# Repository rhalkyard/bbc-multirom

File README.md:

# MultiROM: A low-cost BBC Master / Electron ROM cartridge

There are plenty of perfectly-good options for building ROM cartridges for the BBC Master and Acorn Electron Plus One. However, I am a stubborn git and enjoy reinventing the wheel for fun, so I decided to come up with my own take on the concept.

Rather than use the 27x and 28x series (E)EPROMS that were used Back In The Day, MultiROM uses a NOR Flash IC, the SST39SF010A. This part is much cheaper and more readily available than EEPROMs, but can still be obtained as a through-hole part for easy DIY assembly. Additionally, it offers more capacity (a whopping one megabit!), which MultiROM uses to store multiple ROM images on one cartridge, selected by DIP switches.

The schematic and PCB layout were produced using [KiCad 7.0](https://www.kicad.org/).

## How to build MultiROM

### Bill of Materials

Reference   | Part
------------|-------------------------------------------------------------
`C1`, `C2`  | Ceramic capacitor, 0.1μF
`RN1`       | SIP6 resistor network, bussed, 10KΩ
`SW1`       | SPST DIP switch module, 4 switches
`U1`        | SST39SF010 1Mbit flash memory, DIP32 package
`U2`        | GAL16V8 or ATF16V8 programmable logic device, DIP20 package

`RN1` can be omitted if you trust the weak pull-ups built into `U2`. I forgot to order it when building my prototypes, and they seem to work just fine without it.

`SW1` can be omitted if you want the cartridge to function as a basic 2x16k catridge without bank switching.

### PCB

Any PCB fabricator service such as PCBWay, OSHPark or JLCPCB should be able to fabricate the board. Some shops will accept the `.kicad_pcb` file directly, but most will require Gerber and drill files. These can be exported from Kicad using the File -> Fabrication Outputs menu options.

Ideally, the edge connector should have a chamfered board edge and hard gold-plated contacts, to avoid damaging the PCB socket and to ensure a good connection. These are usually extra-cost options that have to be requested when placing the order.

When assembling components onto the PCB, pay attention to which side they are on! Integrated Circuits `U1` and `U2` go on the *back* side of the PCB, with their orientation notches facing towards the edge connector.

This project uses [KiBot](https://github.com/INTI-CMNB/KiBot) to automate output in various formats from KiCad; release archives contain manufacturing files for various popular PCB fabricators.

### GAL

`U2` is a programmable GAL that provides selection and addressing logic compatible with both the Electron and BBC Master.

GALasm source for `U2` can be found in the `pld/` directory, see [the README in that folder](pld/README.md) for instructions on building and programming.

### Cartridge case

The MultiROM PCB is designed to fit in the 'standard' Master/Electron cartridge case produced by Acorn. I do not have a real cartridge to check this against, but I 3D-printed [Paul Boddie's OpenSCAD cartridge](https://hgweb.boddie.org.uk/AcornElectron) and it fits nicely in there.

If the bank-selection DIP switches (`SW1`) are installed, a suitable cutout will need to be made in the case.

Note that there is very little clearance for components inside the case - if the board is to fit inside the case, then the ICs must be soldered directly onto the board rather than socketed.

## How to use MultiROM

### Inserting the cartridge

With the machine powered off, insert MultiROM into either the front or rear cartridge slot. In the rear slot, MultiROM will appear as Sideways ROMs 0 and 1. In the front slot, it will appear as Sideways ROMs 2 and 3.

Keep in mind that the cartridge housing is the only thing preventing a cartridge from being inserted backwards! If using a bare MultiROM board, pay attention to the "This side to front" markings - the correct orientation is with the chips facing *away* from you.

### Switching banks

Each cartridge slot corresponds to two Sideways ROMs - 0 and 1 for the rear cartridge slot, and 2 and 3 for the front. The DIP switch `SW1` on the front of the cartridge allows one of four banks to be selected for each ROM, allowing multiple ROM images to be stored on the cartridge.

The left two switches select the bank for ROM 0 or 2, the right two switches select the bank for ROM 1 or 3.

While switching banks on a running machine is unlikely to cause any permanent harm, it will almost certainly cause the machine to crash the next time a ROM service call is issued. Always reset the machine after switching banks!

### Programming

#### In-System Programming

The [`tools/`](tools/) directory contains software suitable for either a Master or Electron, that can program MultiROM, query Sideways ROM slots, and save Sideways ROMs to tape or disc.

Source is in [BeebASM](https://github.com/stardot/beebasm) format.

#### Using an external programmer

The flash IC can be programmed in an external programmer according to the following memory map.

Address Range   | ROM       |Bank
----------------|-----------|----
00000-03FFF     | Low       | 0
04000-07FFF     | High      | 0
08000-0BFFF     | Low       | 1
0C000-0FFFF     | High      | 1
10000-13FFF     | Low       | 2
14000-17FFF     | High      | 2
18000-1BFFF     | Low       | 3
1C000-1FFFF     | High      | 3

## Technical details

The SST39SF010A is flash memory, and cannot be programmed like a regular EEPROM. Data can only be erased in 4kb sectors, and writes and erase operations are performed using command strings written to 'magic' addresses. Writes can only be made to erased memory. After issuing an erase or write command, the chip must be allowed to complete the operation before continuing.

Completion can be determined by repeatedly reading back the written byte - until the operation is complete, bit 7 will be inverted, and bit 6 will toggle with each subsequent read.

Since the programming process is so convoluted, and regular writes are ignored, a write protection jumper is not provided.

### Flash Commands

Writing, erasing, chip-status and chip-ID functions are accessed by performing a 'magic' sequence of writes, as described in the datasheet, to addresses `5555` and `2AAA`

Because the cartridge slots are mapped into memory starting at address `&8000`, and the low/high ROM select line is used as the 14th address bit, when programming flash on the machine, use the following addresses:

Flash address   | ROM      | BBC Address
----------------|----------|------------
`5555`          | 1 / 3    | `9555`
`2AAA`          | 0 / 2    | `AAAA`

E.g., to write a byte to ROM 0 (i.e. the low ROM in the front cartridge socket), assuming that the sector has been erased:

1. Page in ROM 1
2. Write `&AA` to `&9555`
3. Page in ROM 0
4. Write `&55` to `&AAAA`
5. Page in ROM 1
6. Write `&A0` to `&9555`
7. Page in ROM 0
8. Write a byte to the desired address
9. Repeatedly read back any ROM address until two consecutive reads yield the same data.

This process must be repeated for each byte.

Any spurious reads or writes occurring during this process will cancel the operation or cause undesirable effects - to prevent MOS from interfering it is advisable to disable IRQ interrupts with an `SEI` instruction.

### Example Code

[`tools/flashio.6502`](tools/flashio.6502) contains utility routines for erasing and programming the flash, and safely querying its ID bytes without corrupting Sideways RAM. These were written for use by the tools in that directory, but are heavily commented and designed to be reused.

## TODO

- [ ] Modify [Paul Boddie's OpenSCAD cartridge case](https://hgweb.boddie.org.uk/AcornElectron) to have a cutout for the DIP switches (and maybe cutouts for IC sockets too?).

- [ ] Recruit a volunteer to test cartridge and software functionality on Electron.

## References

- [Phillip Pearson's Electron flash cartridge](https://github.com/google/myelin-acorn-electron-hardware/tree/main/32kb_flash_cartridge) - uses SST39SF010A, but can't be written on a Master, and does not have bank switching.

- [Stardot thread for Retro Hardware ARA III](https://stardot.org.uk/forums/viewtopic.php?t=15629) - writeable cartridge that uses a GAL to support both Electron and Master, but uses expensive 28C256 EEPROM.

- [BooBip.com Sideways Flash Module](http://www.boobip.com/hardware/128kb-flash) - another SST39SF010A-based ROM replacement, designed to plug into internal Sideways ROM sockets.

- [Acorn Application Note 014: Acorn Electron Cartridge Interface Specification](http://chrisacorns.computinghistory.org.uk/docs/Acorn/AN/014.pdf) - Official cartridge interface specs, including differences between Electron and Master.

- [BeebWiki article on Sideways ROM](https://beebwiki.mdfs.net/Paged_ROM) - especially the section on the Electron and its ROM-selection quirks. See also, this [Stardot post](https://stardot.org.uk/forums/viewtopic.php?p=6681#6681) with a technical background on the Electron's ROM selection register.

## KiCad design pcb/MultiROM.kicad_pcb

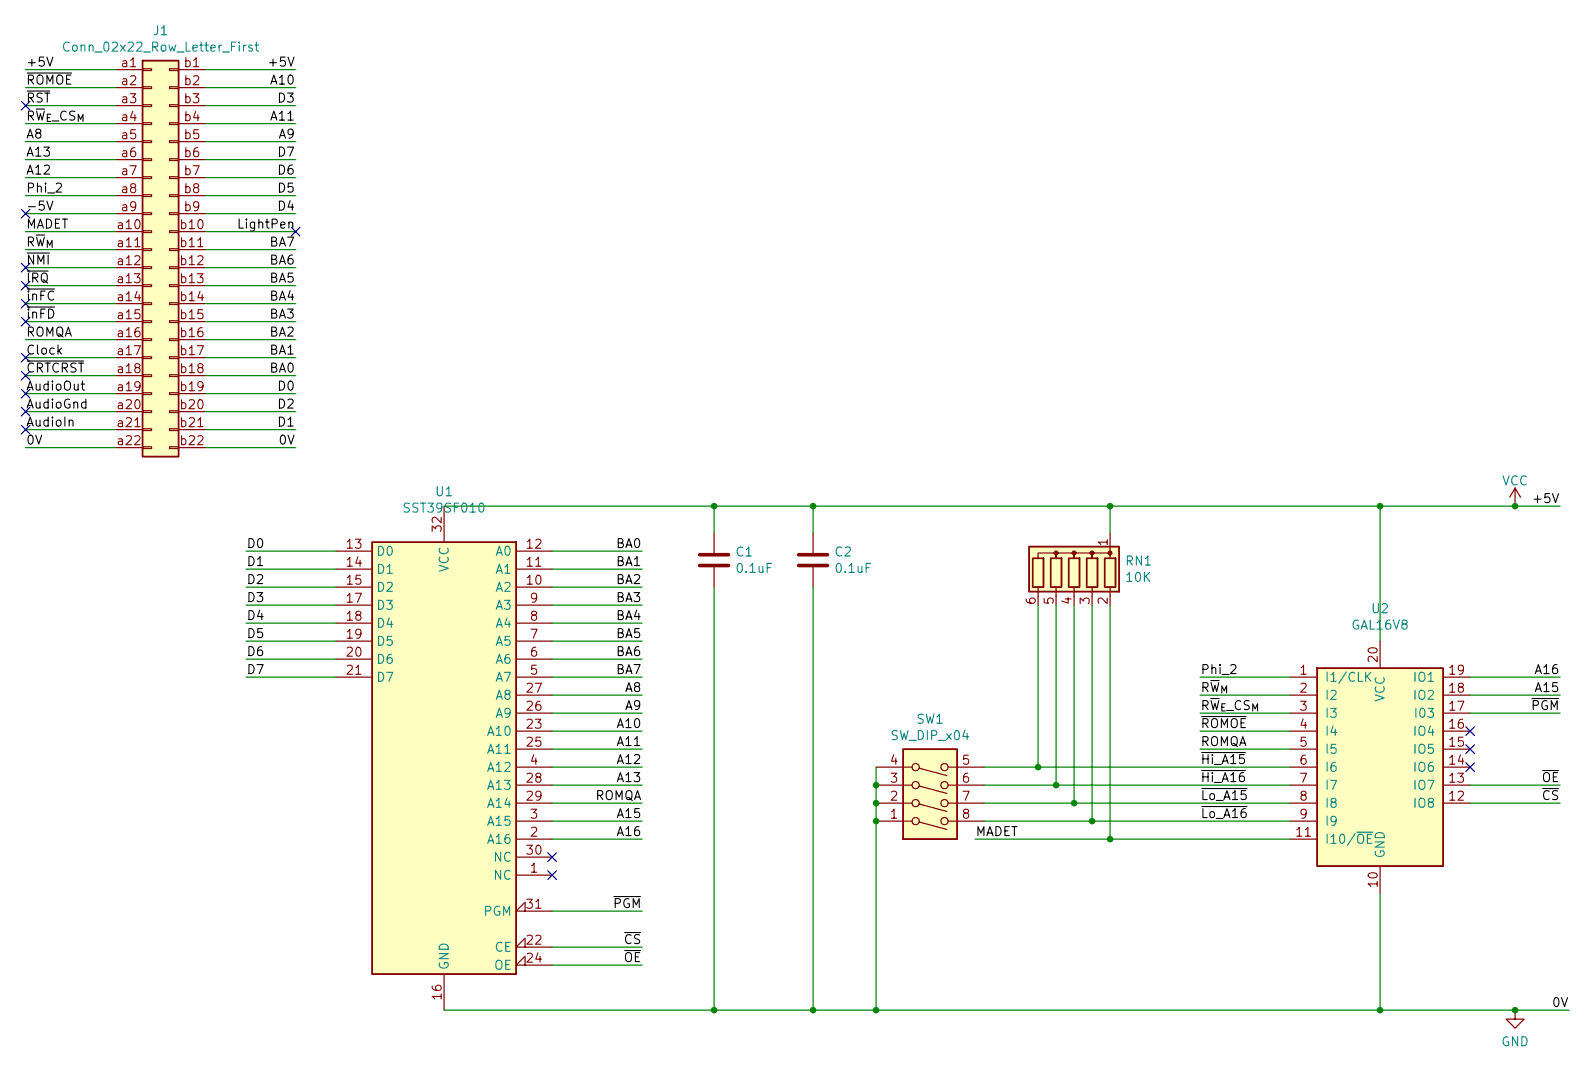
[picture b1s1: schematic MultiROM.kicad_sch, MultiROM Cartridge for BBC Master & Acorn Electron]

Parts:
C1, C2: 0.1uF; C_Disc_D3.0mm_W1.6mm_P2.50mm
J1: Conn_02x22_Row_Letter_First; bbc-master-acorn-electron-cartridge
RN1: 10K; R_Array_SIP6
SW1: SW_DIP_x04; SW_DIP_SPSTx04_Piano_10.8x11.72mm_W7.62mm_P2.54mm
U1: SST39SF010; DIP-32_W15.24mm
U2: GAL16V8; DIP-20_W7.62mm

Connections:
/-5V: J1.a9
/A8: J1.a5, U1.27 (A8)
/A9: J1.b5, U1.26 (A9)
/A10: J1.b2, U1.23 (A10)
/A11: J1.b4, U1.25 (A11)
/A12: J1.a7, U1.4 (A12)
/A13: J1.a6, U1.28 (A13)
/A15: U1.3 (A15), U2.18 (IO2)
/A16: U1.2 (A16), U2.19 (IO1)
/AudioGnd: J1.a20
/AudioIn: J1.a21
/AudioOut: J1.a19
/BA0: J1.b18, U1.12 (A0)
/BA1: J1.b17, U1.11 (A1)
/BA2: J1.b16, U1.10 (A2)
/BA3: J1.b15, U1.9 (A3)
/BA4: J1.b14, U1.8 (A4)
/BA5: J1.b13, U1.7 (A5)
/BA6: J1.b12, U1.6 (A6)
/BA7: J1.b11, U1.5 (A7)
/Clock: J1.a17
/D0: J1.b19, U1.13 (D0)
/D1: J1.b21, U1.14 (D1)
/D2: J1.b20, U1.15 (D2)
/D3: J1.b3, U1.17 (D3)
/D4: J1.b9, U1.18 (D4)
/D5: J1.b8, U1.19 (D5)
/D6: J1.b7, U1.20 (D6)
/D7: J1.b6, U1.21 (D7)
/LightPen: J1.b10
/MADET: J1.a10, RN1.2 (R1), U2.11 (I10/~OE)
/Phi_2: J1.a8, U2.1 (I1/CLK)
/ROMQA: J1.a16, U1.29 (A14), U2.5 (I5)
/R~W_{E}_CS_{M}: J1.a4, U2.3 (I3)
/R~W_{M}: J1.a11, U2.2 (I2)
/~CRTCRST: J1.a18
/~CS: U1.22 (CE), U2.12 (IO8)
/~Hi_A15: RN1.6 (R5), SW1.5, U2.6 (I6)
/~Hi_A16: RN1.5 (R4), SW1.6, U2.7 (I7)
/~IRQ: J1.a13
/~Lo_A15: RN1.4 (R3), SW1.7, U2.8 (I8)
/~Lo_A16: RN1.3 (R2), SW1.8, U2.9 (I9)
/~NMI: J1.a12
/~OE: U1.24 (OE), U2.13 (IO7)
/~PGM: U1.31 (PGM), U2.17 (I03)
/~ROMOE: J1.a2, U2.4 (I4)
/~RST: J1.a3
/~inFC: J1.a14
/~inFD: J1.a15
GND: C1.2, C2.2, J1.a22, J1.b22, SW1.1, SW1.2, SW1.3, SW1.4, U1.16 (GND), U2.10 (GND)
VCC: C1.1, C2.1, J1.a1, J1.b1, RN1.1 (common), U1.32 (VCC), U2.20 (VCC)

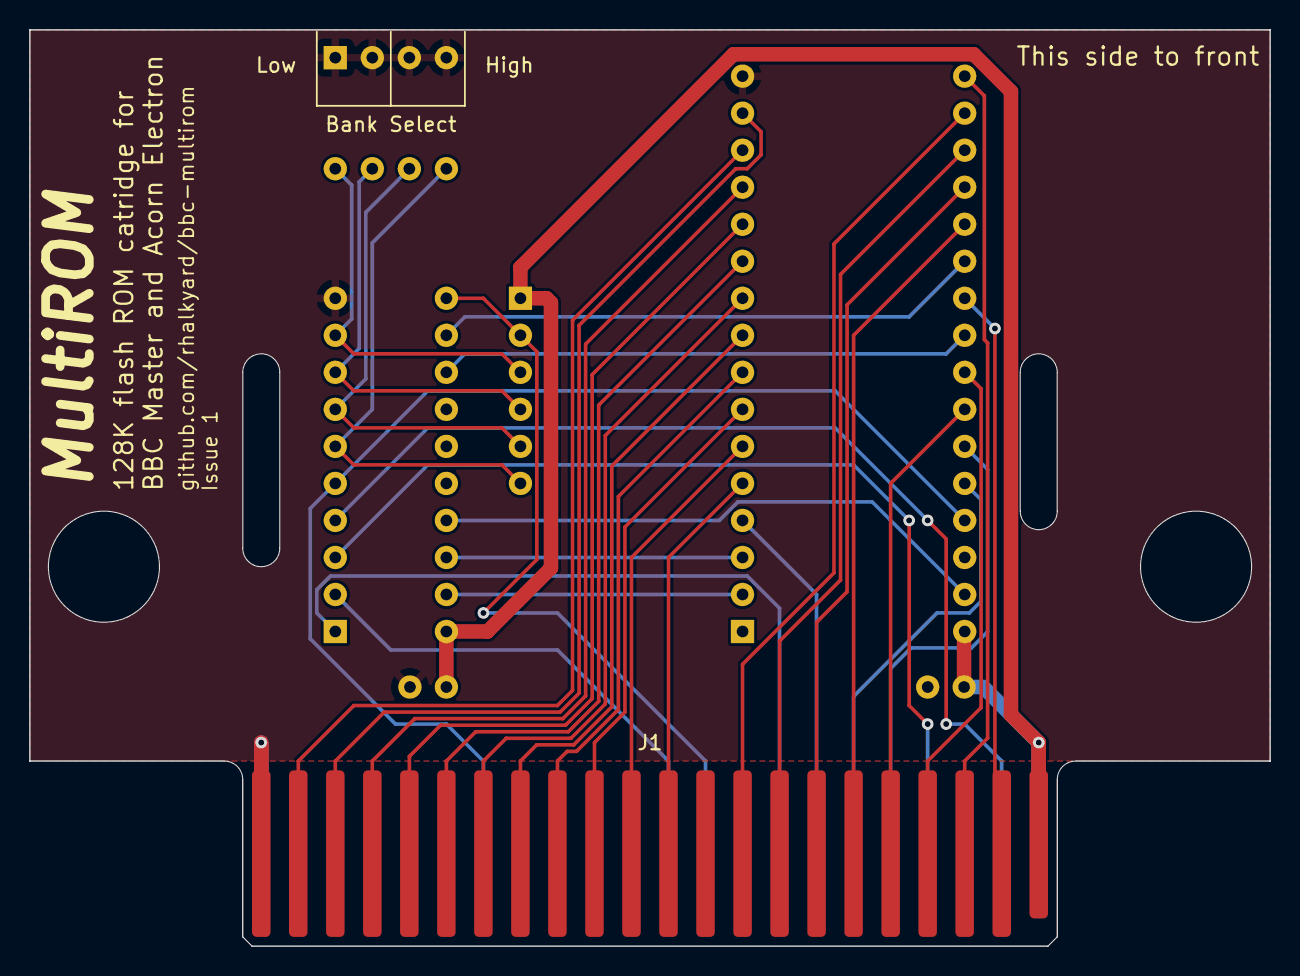
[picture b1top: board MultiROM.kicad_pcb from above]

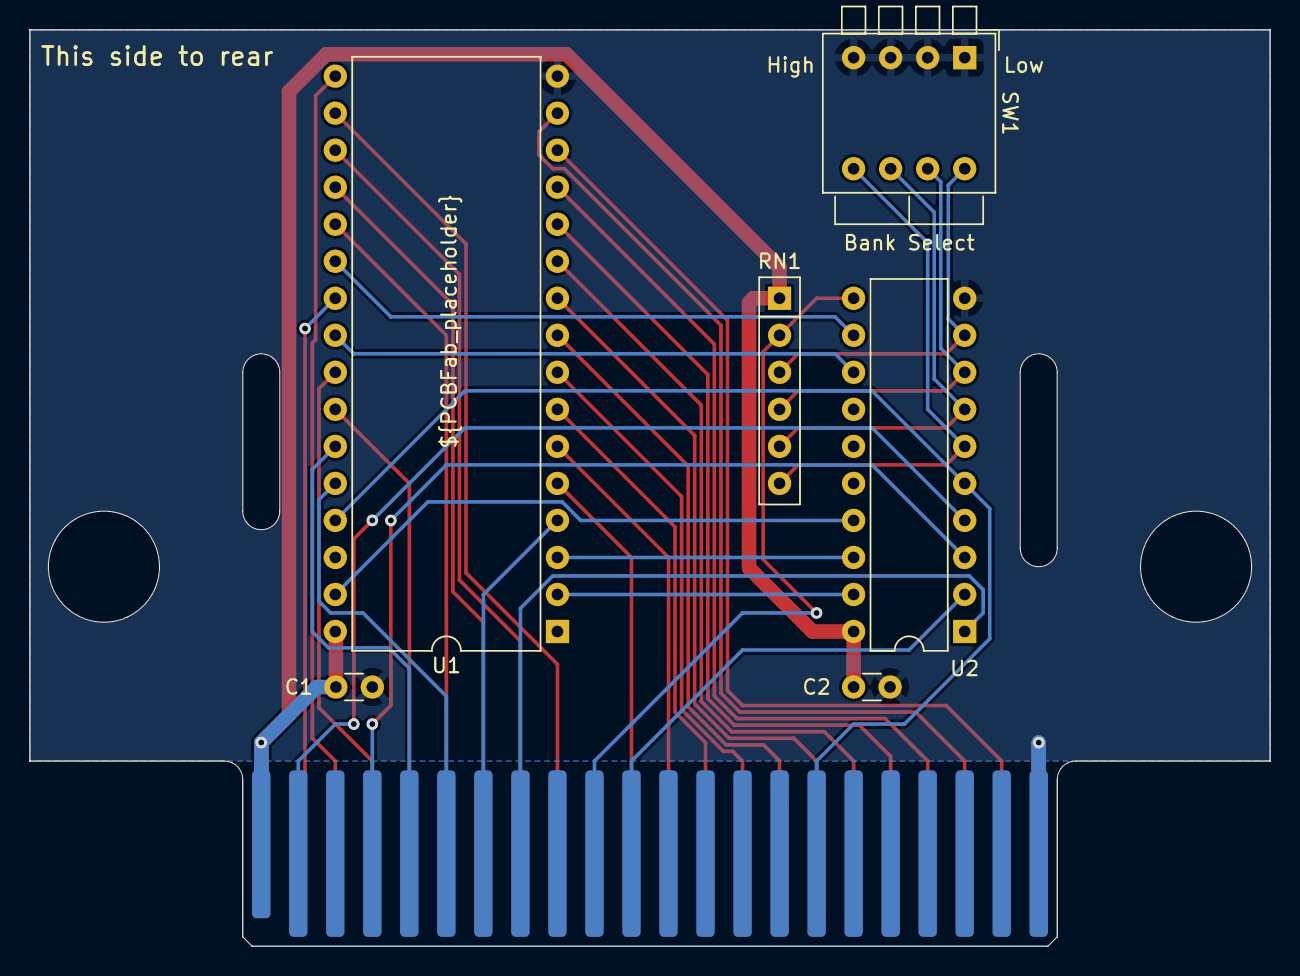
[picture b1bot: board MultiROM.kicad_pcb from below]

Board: 2 copper layers, 85.1 x 62.9 mm, 7 parts (6 on the bottom side), 39 nets.

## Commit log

2023-03-21 Prototype #1 as-built
2023-03-21 PCB revisions post proto#1
2023-03-21 Add GALasm source
2023-03-21 Move PCB into separate directory
2023-03-21 Add miniprog
2023-03-21 add chip-erase
2023-03-21 add tube check
2023-03-21 add rom lister
2023-03-21 listroms tool and miniprog fixes
2023-03-21 Make tools nicer
2023-03-21 PLD bugfix
2023-03-21 Harmonise PLD pin names between CUPL and GALasm
2023-03-21 Tidy up flashio routines
2023-03-21 cartprg: add progress indicator
2023-03-21 PCB+netlist tidyup
2023-03-21 Prefer galasm
2023-03-21 Placeholder text for fab info
2023-03-21 Big Readme Update
2023-03-21 Rename cartridge footprint+library to avoid spaces
2023-03-21 Build system
2023-03-21 git versioning update
2023-03-21 keep version string empty until populated
2023-03-21 Correct order of ROM paging switches
2023-03-21 modular build system
2023-03-21 Give up on PCB text variables for now
2023-03-21 Redo PCB variables
2023-03-21 ignore kibot log
2023-03-21 Add fab outputs to build target
2023-03-21 Use edge-style DIP switch
2023-03-21 Exclude edge connector from BOM
2023-03-21 Add images to README
2023-03-21 Move front switch labels to sides
2023-03-21 Issue 1
